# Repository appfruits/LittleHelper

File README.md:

# LittleHelper
This is the Arduino compatible firmware running Little Helper, a little device that is useful in electronic labs. The firmware also shows how to build a more complex LCD based application, featuring a few standard controls.

This software should compile and run on a Teensy 3.1 although you will need a few hardware components to make use of it. Have a look at http://www.appfruits.com/littlehelper. We provide everything from PCB schematics and layout, even enclosings to build your own Little Helper or getting inspired building your own little, useful device.

Copyright 2014-2015 by Phillip Schuster
http://www.appfruits.com

## Hardware
We also added the Eagle PCBs Design, layout and schematics. We also added the Copper file. Copper is a Mac applications that makes it easy to generate 3D models of your Eagle based PCBs and also helps in building a BOM and keeping it up to date. Have a look at http://www.copper-app.com.

## Structure
This software is C++ and shows how to build a nice, stack based application runloop and User Interface that is easily expandable by providing standard controls and protocols and uses the good old MVC structure. 

Running such code on a small 8-bit AVR is overkill, but with all those new ARM MCUs offering a lot of performance, and more importantly offering more RAM allows such code to be written and run even on small devices. This makes it easier to write structured software that you can read in a couple of months from now.

## License
We provide this in a MIT-License. You may use, copy, modify, merge, publish, distribute, sublicense, and/or sell copies of the Software but you must include this copyright notice and this permission in all copies or substantial portions of the Software.

We invest time and resources making this open source. Please support us by spreading your word and purchasing our products.

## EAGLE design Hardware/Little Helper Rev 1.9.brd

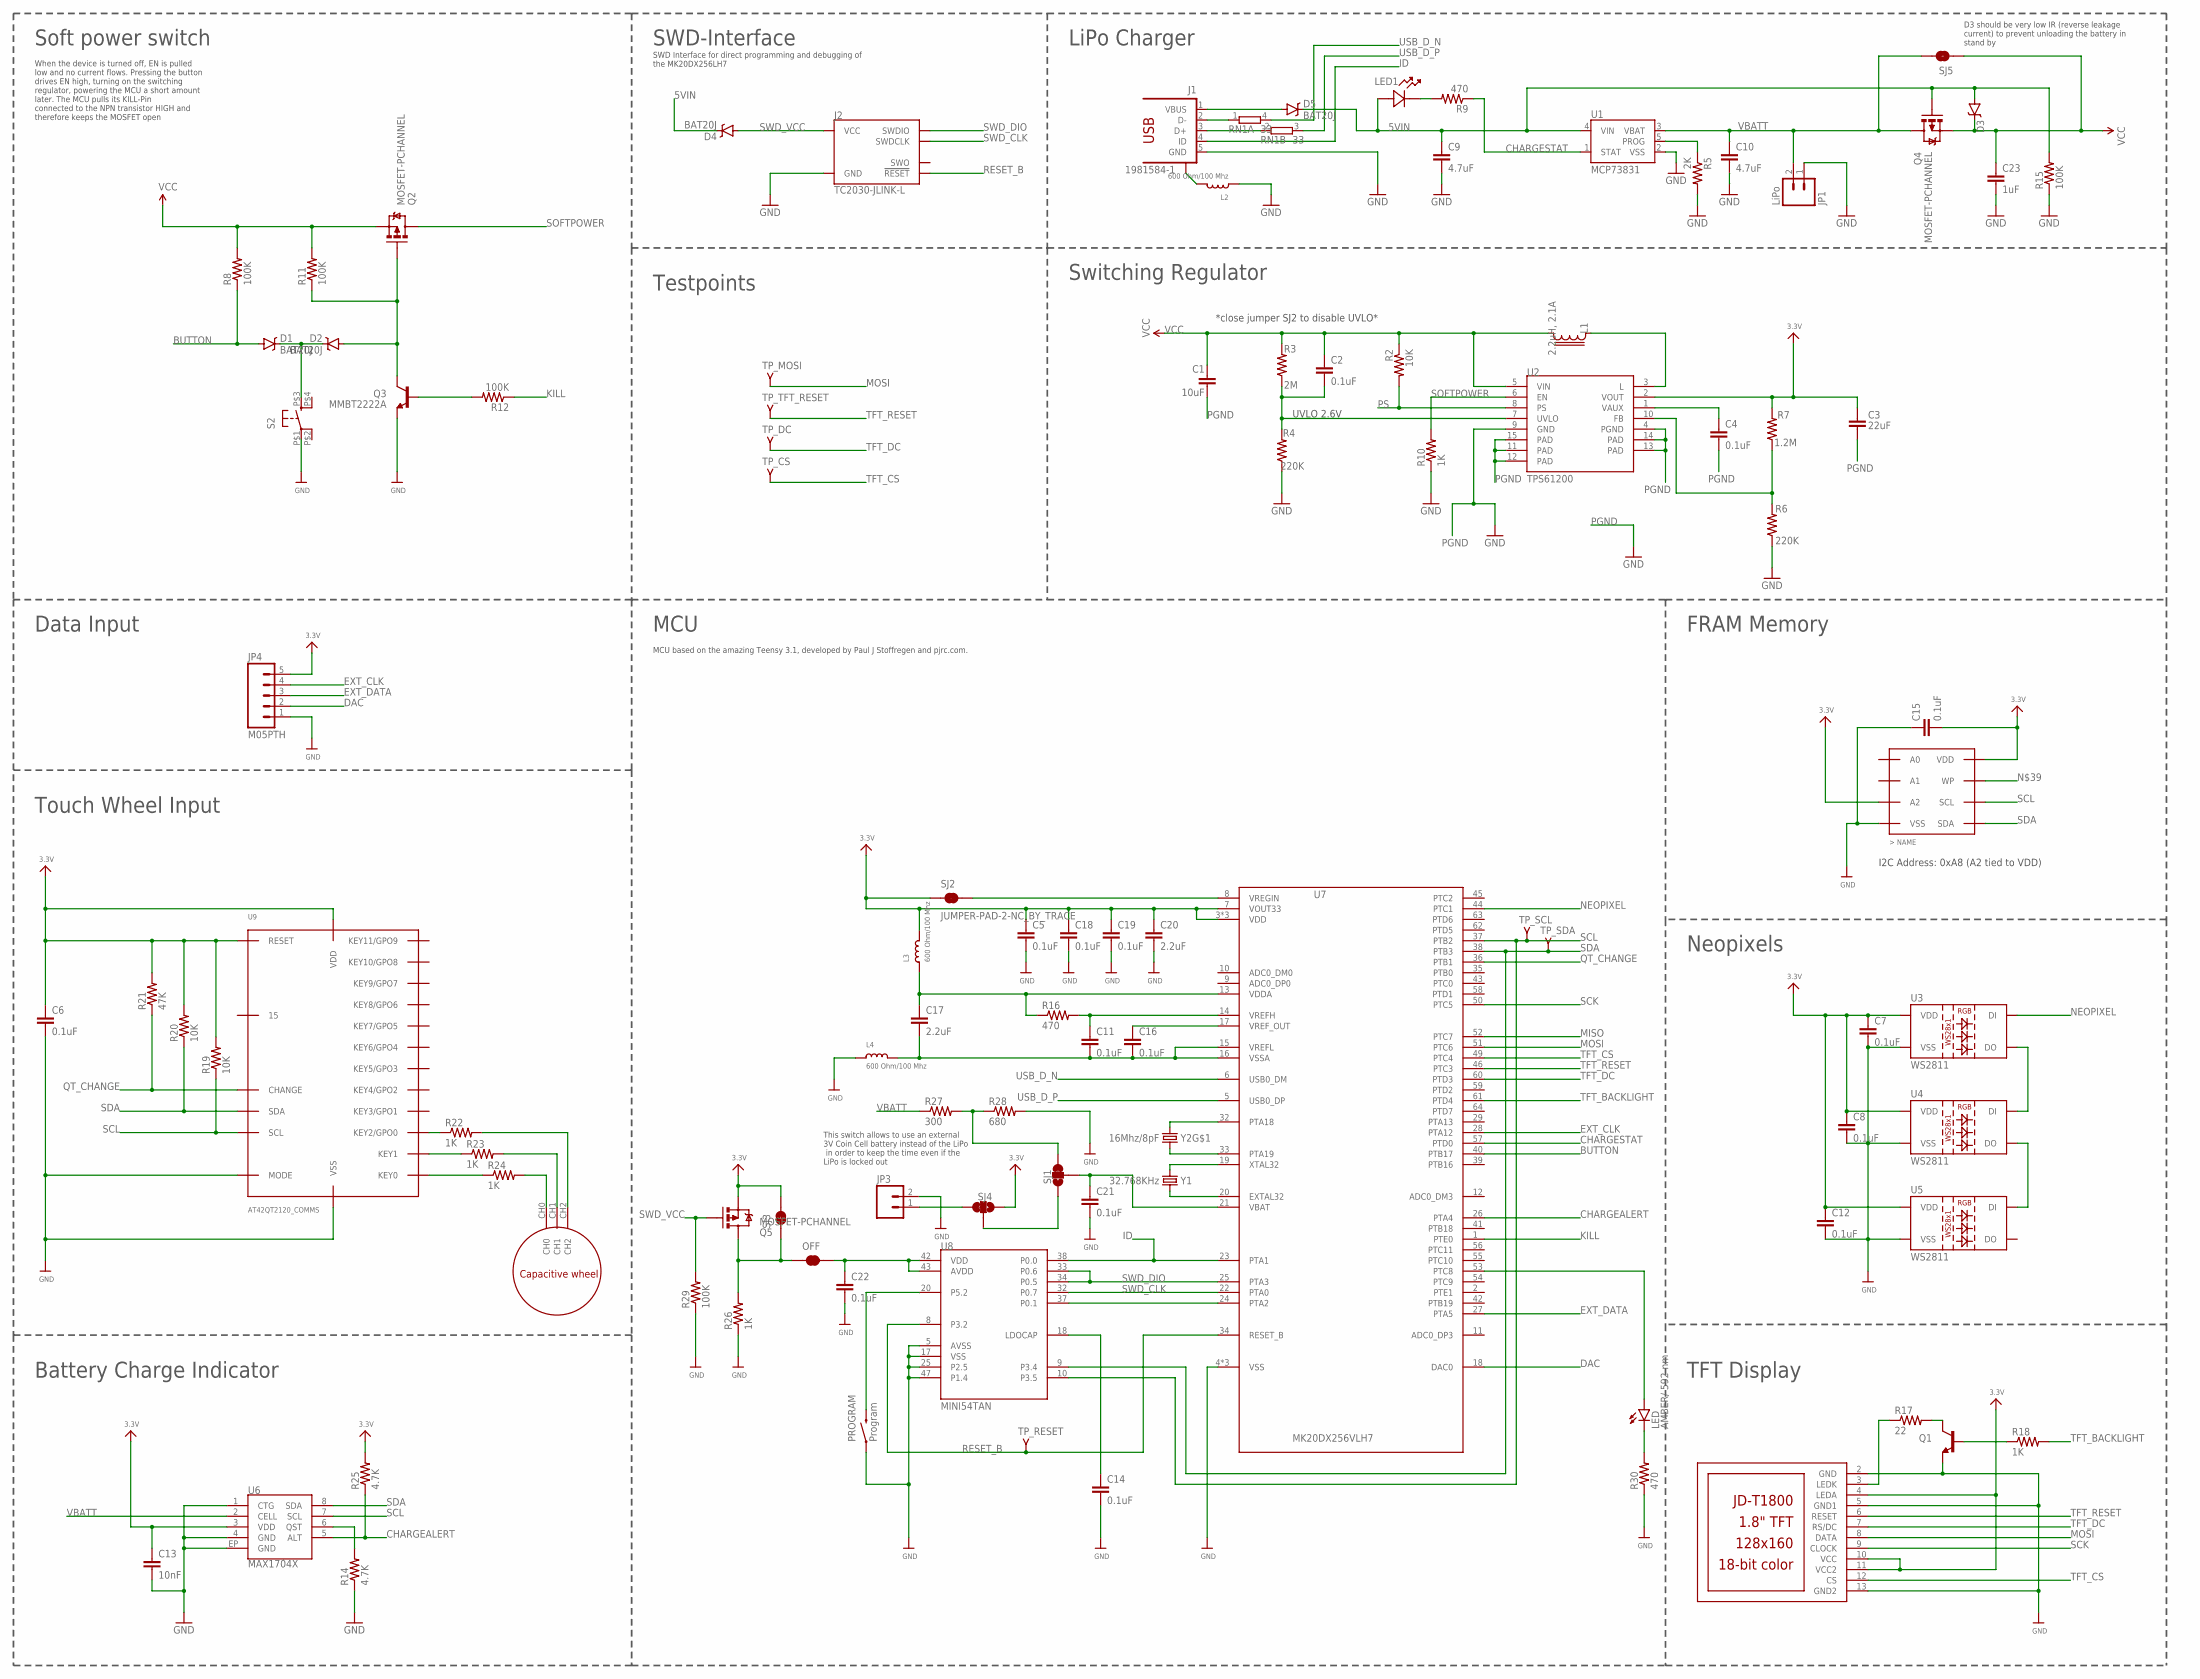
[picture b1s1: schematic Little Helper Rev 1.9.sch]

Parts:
C1: 10uF; 0603-CAP
C2, C4, C5, C6, C7, C8, C11, C12, C14, C15, C16, C18, C19, C21, C22: 0.1uF; 0603-CAP
C3: 22uF; 0603-CAP
C9, C10: 4.7uF; 0603-CAP
C13: 10nF; 0603-CAP; MPN C0603C103K5RACTU
C17, C20: 2.2uF; 0603-CAP
C23: 1uF; 0603-CAP
D1, D2, D4, D5: BAT20J; SOD-323
D3: DIODE-SCHOTTKY-LOW_LEAKAGE; SOD-323
J1: 1981584-1; MPN ZX62-AB-5PA(11)
J2: TC2030-JLINK-L; TC2030-IDC
JP1: LiPo; JST-2-SMD
JP3: M02PTH; 1X02
JP4: M05PTH; 1X05
L1: 2.2uH, 2.1A; LPS3015
L2, L3, L4: 600 Ohm/100 Mhz; 0805
LCD1: JD-T1800
LED: AMBER/ 592 nm; LED-0603
LED1: 597-2311-407F; LED_597-2311-407F
OFF: JUMPER-PAD-2-NC_BY_TRACE; PAD-JUMPER-2-NC_BY_TRACE_YES_SILK
PROGRAM: Program; TACTILE-SWITCH-1101NE; MPN RS-282G05A3-SM RT
Q1: TRANSISTOR_NPNSOT23-3; SOT23-3
Q2, Q4, Q5: MOSFET-PCHANNEL; SOT23-3; MPN BSS84LT1G
Q3: MMBT2222A; SOT23-3
R2, R19, R20: 10K; 0603-RES
R3: 2M; 0603-RES
R4, R6: 220K; 0603-RES
R5: 2K; 0603-RES
R7: 1.2M; 0603-RES
R8, R11, R12, R15, R29: 100K; 0603-RES
R9, R16, R30: 470; 0603-RES
R10, R18, R22, R23, R24, R26: 1K; 0603-RES
R14, R25: 4.7K; 0603-RES
R17: 22; 0603-RES
R21: 47K; 0603-RES
R27: 300; 0603-RES
R28: 680; 0603-RES
RN1: 33; EXB34V; MPN EXB-34V330JV
S2: TAC_SWITCHPTS645_SERIES; PTS645_BUTTON_SERIES; MPN PTS645SH50SMTR 92 LFS
SJ1, SJ4: JUMPER-PAD-3-2OF3_NC_BY_TRACE; PAD-JUMPER-3-2OF3_NC_BY_TRACE_YES_SILK_FULL_BOX
SJ2: JUMPER-PAD-2-NC_BY_TRACE; PAD-JUMPER-2-NC_BY_TRACE_YES_SILK
SJ3, SJ5: JUMPER-PAD-2-NOYES_SILK; PAD-JUMPER-2-NO_YES_SILK
TP_CS: TPV-PAD-016; PAD-016
TP_DC: TPV-PAD-016; PAD-016
TP_MOSI: MOSI; PAD-016
TP_RESET: TPV-PAD-016; PAD-016
TP_SCL: TPV-PAD-016; PAD-016
TP_SDA: TPV-PAD-016; PAD-016
TP_TFT_RESET: MOSI; PAD-016
U1: MCP73831; SOT23-5; MPN MCP73831T-2ACI/OT
U2: TPS61200; QFN-10_PAD
U3, U4, U5: WS2811; LED-TRICOLOR-5050-IC
U6: MAX1704X; TDFN-8
U7: MK20DX256VLH7; MPN MK20DX256VLH7
U8: MINI54TAN
U9: AT42QT2120_COMMS; QT2120
U12: FM24CL64BSOIC8_150MIL; SO08
U$1: QTWHEEL_MODULE; QTWHEELMODULE
Y1: 32.768KHz; CRYSTAL-TXC-7A; MPN FC-255 32.7680K-A3
Y2: 16Mhz/8pF; CRYSTAL-SMD-5X3; MPN ECS-160-8-30B-CKM

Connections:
3.3V: C3.1, C5.1, C6.1, C7.1, C8.1, C12.1, C13.1, C15.2, C18.1, C19.1, C20.1, JP4.5, L3.2, LCD1.4 (LEDA), LCD1.10 (VCC), LCD1.11 (VCC2), Q5.2 (S), R7.2, R19.2, R20.2, R21.2, R25.2, SJ2.1, SJ3.2, SJ4.1, U2.2 (VOUT), U3.3 (VDD), U3.5 (VDD), U4.3 (VDD), U4.5 (VDD), U5.3 (VDD), U5.5 (VDD), U6.3 (VDD), U7.3 (VDD), U7.7 (VOUT33), U7.30 (VDD), U7.48 (VDD), U9.11 (VDD), U9.14 (RESET), U12.3 (A2), U12.8 (VDD)
5VIN: C9.1, D3.A, D4.C, D5.C, LED1.2, Q4.1 (G), R15.2, U1.4 (VIN)
BUTTON: D1.A, R8.1, U7.40 (PTB17)
CHARGEALERT: R25.1, U6.5 (ALT), U7.26 (PTA4)
CHARGESTAT: R9.1, U1.1 (STAT), U7.57 (PTD0)
DAC: JP4.2, U7.18 (DAC0)
EXT_CLK: JP4.4, U7.28 (PTA12)
EXT_DATA: JP4.3, U7.27 (PTA5)
FB: R6.2, R7.1, U2.10 (FB)
GND: C5.2, C6.2, C7.2, C8.2, C9.2, C10.2, C12.2, C13.2, C14.2, C15.1, C18.2, C19.2, C20.2, C21.2, C22.2, C23.2, J1.5 (GND), J2.5 (GND), JP1.1 (2), JP3.2, JP4.1, L2.1, L4.1, LCD1.2 (GND), LCD1.5 (GND1), LCD1.13 (GND2), PROGRAM.P$1 (1), Q1.2 (E), Q3.2 (E), R4.1, R5.2, R6.1, R10.1, R14.1, R15.1, R26.1, R28.2, R29.1, R30.1, S2.P$1 (1), U1.2 (VSS), U3.6 (VSS), U4.6 (VSS), U5.6 (VSS), U6.1 (CTG), U6.4 (GND), U6.EP (GND), U7.4 (VSS), U7.31 (VSS), U7.47 (VSS), U8.5 (AVSS), U8.17 (VSS), U8.25 (P2.5), U8.47 (P1.4), U9.10 (VSS), U9.12 (MODE), U12.4 (VSS)
ID: J1.4 (ID), U7.23 (PTA1), U8.38 (P0.0)
KILL: R12.1, U7.1 (PTE0)
MISO: U7.52 (PTC7)
MOSI: LCD1.8 (DATA), TP_MOSI.1, U7.51 (PTC6)
unnamed: OFF.1, Q5.3 (D), R26.2, SJ3.1
unnamed: L1.1, U2.3 (L)
unnamed: D2.A, Q2.1 (G), Q3.3 (C), R11.1
unnamed: Q3.1 (B), R12.2
unnamed: D1.C, D2.C, S2.P$3 (3)
unnamed: LED1.1, R9.2
unnamed: C21.1, SJ1.2, U7.21 (VBAT)
unnamed: C22.1, OFF.2, U8.42 (VDD), U8.43 (AVDD)
unnamed: R5.1, U1.5 (PROG)
unnamed: LED.A, U7.53 (PTC8)
unnamed: D5.A, J1.1 (VBUS)
unnamed: JP3.1, SJ4.3
unnamed: U7.24 (PTA2), U8.37 (P0.1)
unnamed: R22.1, U9.7 (KEY2/GPO0)
unnamed: R23.1, U9.8 (KEY1)
unnamed: LED.C, R30.2
unnamed: PROGRAM.P$2 (2), U8.20 (P5.2)
unnamed: SJ1.1, SJ4.2
unnamed: C14.1, U8.18 (LDOCAP)
unnamed: U7.32 (PTA18), Y2.3 (2)
unnamed: U7.33 (PTA19), Y2.1
unnamed: U7.19 (XTAL32), Y1.P$2 (2)
unnamed: U7.20 (EXTAL32), Y1.P$1 (1)
unnamed: R27.2, R28.1, SJ1.3
unnamed: LCD1.3 (LEDK), R17.1
unnamed: R24.1, U9.9 (KEY0)
unnamed: U3.1 (DO), U4.2 (DI)
unnamed: Q1.3 (C), R17.2
unnamed: Q1.1 (B), R18.1
unnamed: R22.2, U$1.CH2
unnamed: R23.2, U$1.CH1
unnamed: R24.2, U$1.CH0
unnamed: U4.1 (DO), U5.2 (DI)
unnamed: R14.2, U6.6 (QST)
NEOPIXEL: U3.2 (DI), U7.44 (PTC1)
PGND: C1.2, C3.2, C4.2, U2.4 (PGND), U2.9 (GND), U2.11 (PAD), U2.12 (PAD), U2.13 (PAD), U2.14 (PAD), U2.15 (PAD)
PS: R2.2, U2.8 (PS)
QT_CHANGE: R21.1, U7.36 (PTB1), U9.17 (CHANGE)
RESET_B: J2.3 (!RESET), TP_RESET.1, U7.34 (RESET_B), U8.8 (P3.2)
SCK: LCD1.9 (CLOCK), U7.50 (PTC5)
SCL: R19.1, TP_SCL.1, U6.7 (SCL), U7.37 (PTB2), U8.10 (P3.5), U9.16 (SCL), U12.6 (SCL)
SDA: R20.1, TP_SDA.1, U6.8 (SDA), U7.38 (PTB3), U8.9 (P3.4), U9.13 (SDA), U12.5 (SDA)
SOFTPOWER: Q2.3 (D), R10.2, U2.6 (EN)
SWD_CLK: J2.4 (SWDCLK), U7.22 (PTA0), U8.32 (P0.7)
SWD_DIO: J2.2 (SWDIO), U7.25 (PTA3), U8.33 (P0.6), U8.34 (P0.5)
SWD_VCC: D4.A, J2.1 (VCC), Q5.1 (G), R29.2
TFT_BACKLIGHT: R18.2, U7.61 (PTD4)
TFT_CS: LCD1.12 (CS), TP_CS.1, U7.49 (PTC4)
TFT_DC: LCD1.7 (RS/DC), TP_DC.1, U7.60 (PTD3)
TFT_RESET: LCD1.6 (RESET), TP_TFT_RESET.1, U7.46 (PTC3)
USB_CON_N: J1.2 (D-), RN1.1
USB_CON_P: J1.3 (D+), RN1.2 (1)
USB_D_N: RN1.4 (2), U7.6 (USB0_DM)
USB_D_P: RN1.3 (2), U7.5 (USB0_DP)
USB_SHIELD: J1.S1, L2.2
UVLO: C2.2, R3.1, R4.2, U2.7 (UVLO)
VAUX: C4.1, U2.1 (VAUX)
VBATT: C10.1, JP1.2 (1), Q4.3 (D), R27.1, SJ5.2, U1.3 (VBAT), U6.2 (CELL)
VCC: C1.1, C2.1, C23.1, D3.C, L1.2, Q2.2 (S), Q4.2 (S), R2.1, R3.2, R8.2, R11.2, SJ5.1, U2.5 (VIN)
VDDA: C17.1, L3.1, R16.1, U7.13 (VDDA)
VREFH: C11.1, R16.2, U7.14 (VREFH)
VREFL: C11.2, C16.2, C17.2, L4.2, U7.15 (VREFL), U7.16 (VSSA)
VREF_OUT: C16.1, U7.17 (VREF_OUT)
VREGIN: SJ2.2, U7.8 (VREGIN)

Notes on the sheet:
UVLO 2.6V
*close jumper SJ2 to disable UVLO*
LiPo Charger
Switching Regulator
Data Input
This switch allows to use an external 3V Coin Cell battery instead of the LiPo in order to keep the time even if the LiPo is locked out
When the device is turned off, EN is pulled low and no current flows. Pressing the button drives EN high, turning on the switching regulator, powering the MCU a short amount later. The MCU pulls its KILL-Pin connected to the NPN transistor HIGH and therefore keeps the MOSFET open
I2C Address: 0xA8 (A2 tied to VDD)
Soft power switch
Battery Charge Indicator
Touch Wheel Input
MCU
FRAM Memory
Neopixels
TFT Display
MCU based on the amazing Teensy 3.1, developed by Paul J Stoffregen and pjrc.com.
SWD Interface for direct programming and debugging of the MK20DX256LH7
SWD-Interface
Testpoints
D3 should be very low IR (reverse leakage current) to prevent unloading the battery in stand by

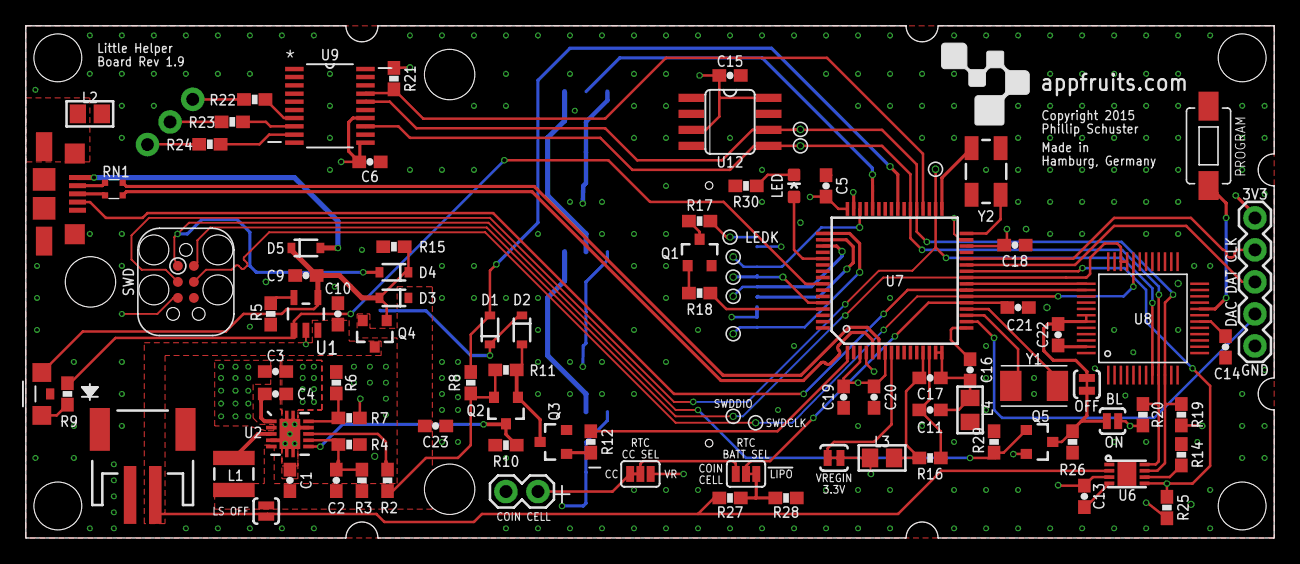
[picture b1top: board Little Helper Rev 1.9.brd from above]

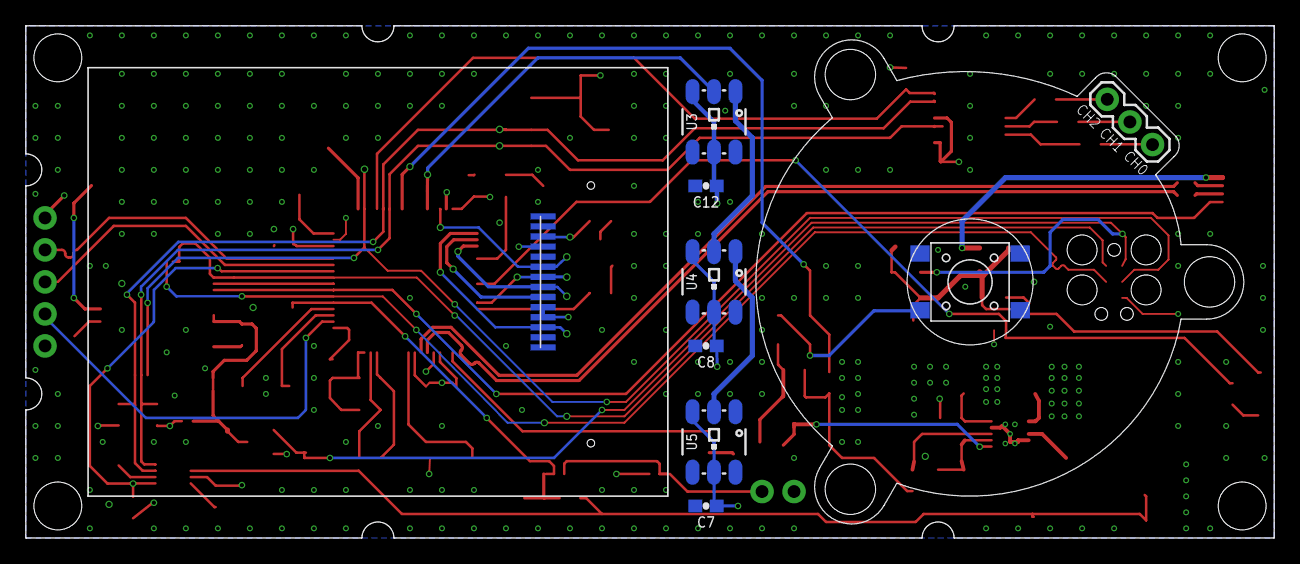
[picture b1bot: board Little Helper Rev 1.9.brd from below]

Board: 4 copper layers, 99.1 x 40.6 mm, 102 parts (9 on the bottom side), 77 nets.

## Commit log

2015-12-14 Initial Import
    This is the initial import into this Github Repository.
2015-12-14 Added Copyright notice
2015-12-14 Added Eagle files and reorganized repository
2015-12-14 Moved Readme and License
2017-02-24 Updated Copper settings
    Updated Copper settings for better compatibility with Copper for iOS.

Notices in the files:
Hardware/Little Helper Rev 1.9.brd:
Copyright 2015
parts and their libraries:
SparkFun-Connectors: Licensing: Creative Commons ShareAlike 4.0 International - https://creativecommons.org/licenses/by-sa/4.0
con-usb: Copyright (C) 2008, Bob Starr
